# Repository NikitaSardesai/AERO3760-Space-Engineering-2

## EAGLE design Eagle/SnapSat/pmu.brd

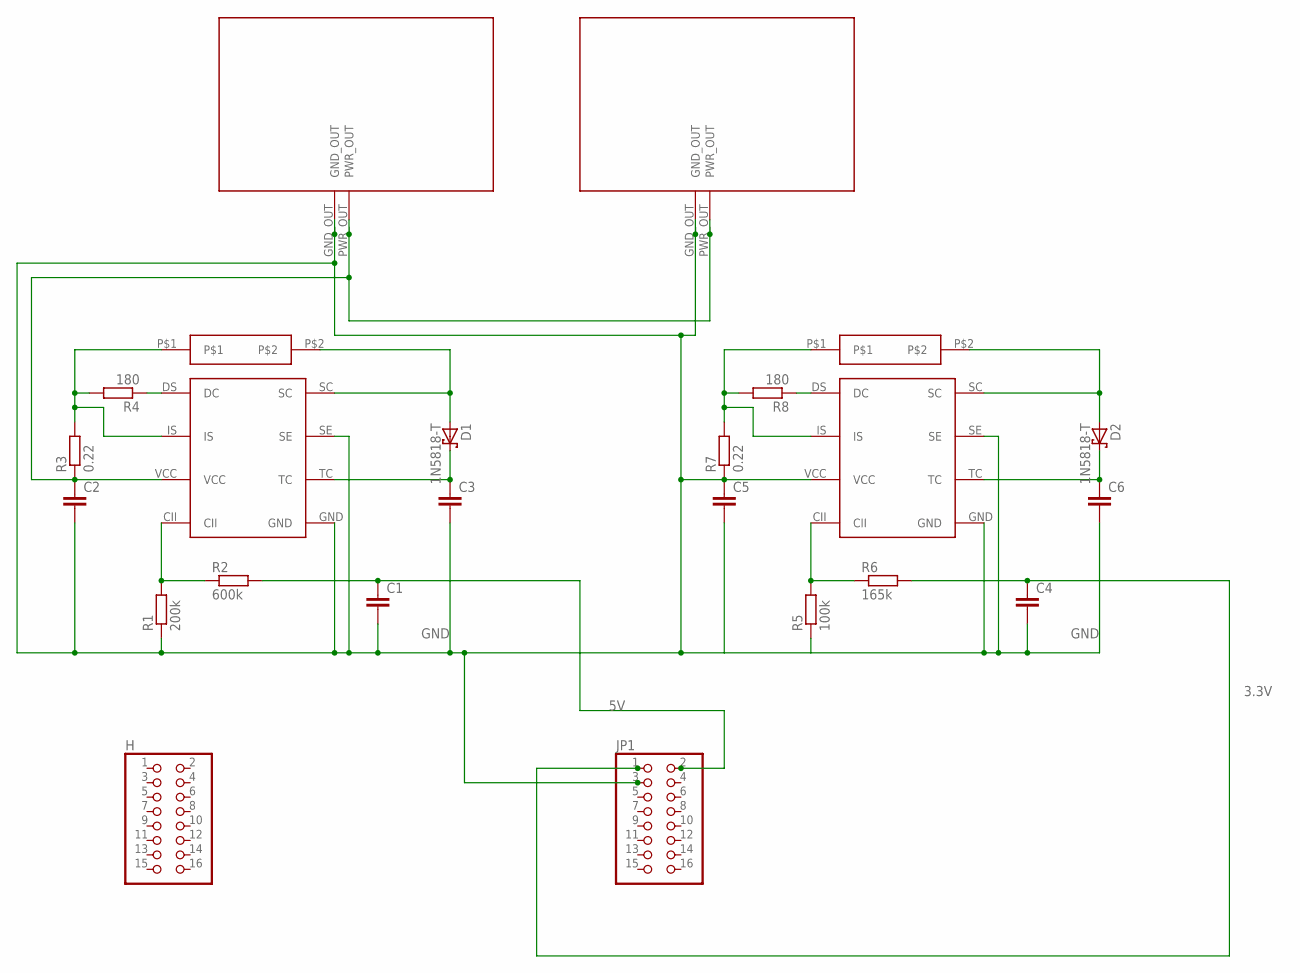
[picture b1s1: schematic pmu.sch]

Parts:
C1, C2, C3, C4, C5, C6: C2.5/6; C2.5-6
D1, D2: 1N5818-T; DO41-7.6
H: PINHD-2X8; 2X08
JP1: PINHD-2X8; 2X08
R1: 200k; 0207/12
R2: 600k; 0207/12
R3, R7: 0.22; 0207/12
R4, R8: 180; 0207/12
R5: 100k; 0207/12
R6: 165k; 0207/12
U$1, U$2: CHAR
U$3, U$5: TIBB
U$4, U$6: IND; 8RHT2

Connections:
3.3V: C4.1, JP1.1, R6.2
5V: C1.1, JP1.2, R2.2
GND: C1.2, C2.2, C3.2, C4.2, C5.1, C5.2, C6.2, JP1.3, R1.1, R5.1, R7.1, U$1.GND_OUT, U$2.GND_OUT, U$3.GND, U$3.SE, U$5.GND, U$5.SE, U$5.VCC
unnamed: D1.A, U$3.SC, U$4.P$2
unnamed: C2.1, R3.1, U$1.PWR_OUT, U$2.PWR_OUT, U$3.VCC
unnamed: R1.2, R2.1, U$3.CII
unnamed: R4.1, U$3.DS (DC)
unnamed: C3.1, D1.C, U$3.TC
unnamed: R5.2, R6.1, U$5.CII
unnamed: R3.2, R4.2, U$3.IS, U$4.P$1
unnamed: R7.2, R8.2, U$5.IS, U$6.P$1
unnamed: R8.1, U$5.DS (DC)
unnamed: D2.A, U$5.SC, U$6.P$2
unnamed: C6.1, D2.C, U$5.TC

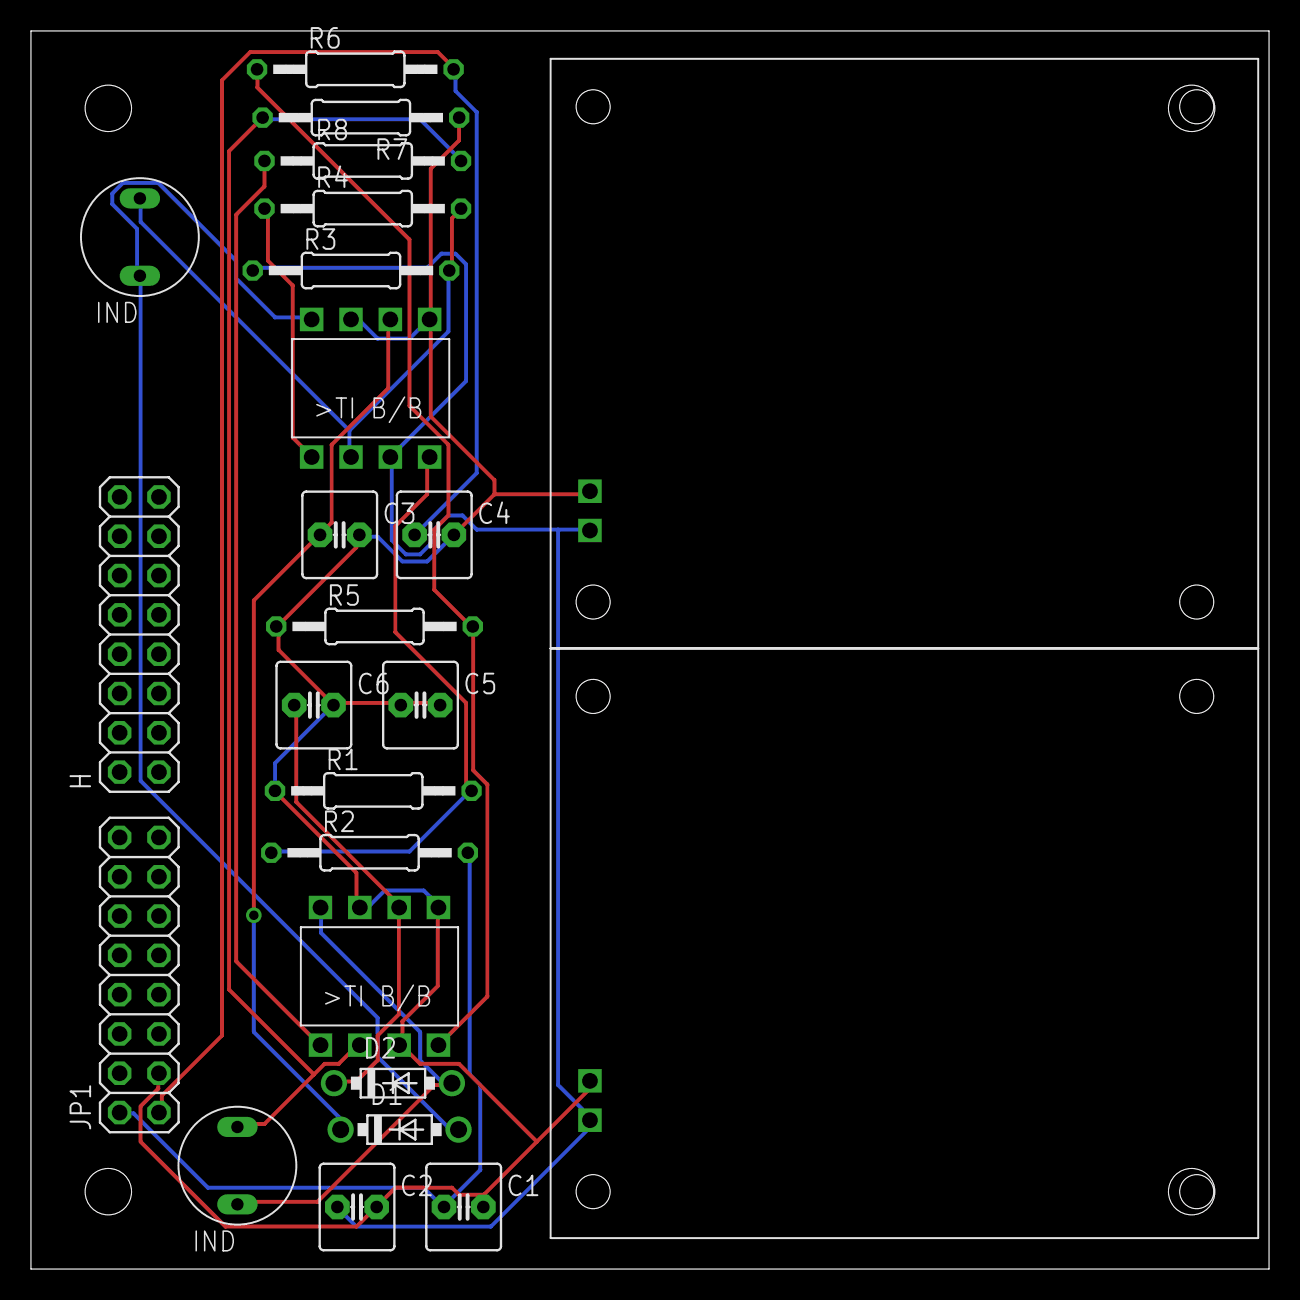
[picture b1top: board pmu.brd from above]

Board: 2 copper layers, 80.0 x 80.0 mm, 24 parts (0 on the bottom side), 14 nets.

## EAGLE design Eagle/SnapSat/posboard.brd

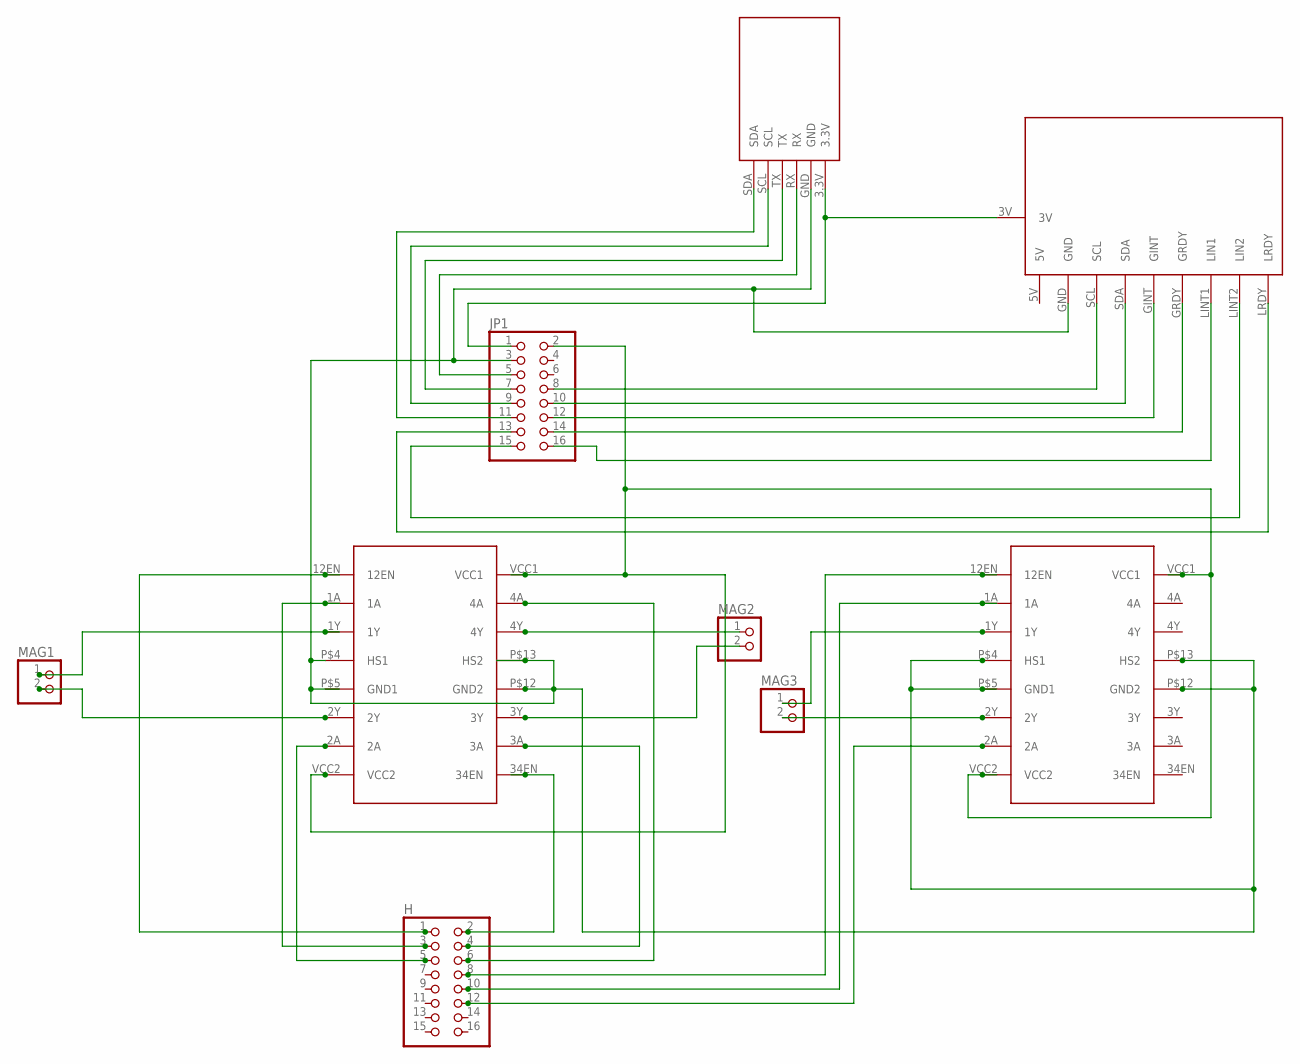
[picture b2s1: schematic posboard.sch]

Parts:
H: PINHD-2X8; 2X08
JP1: PINHD-2X8; 2X08
MAG1, MAG2, MAG3: PINHD-1X2; 1X02
U$1: GPS
U$2: IMU
U$3, U$4: HBRIDGE

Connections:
unnamed: JP1.1, U$1.3.3V, U$2.3V
unnamed: JP1.3, U$1.GND, U$2.GND, U$3.P$4 (HS1), U$3.P$12 (GND2), U$3.P$13 (HS2), U$4.P$4 (HS1), U$4.P$5 (GND1), U$4.P$12 (GND2), U$4.P$13 (HS2)
unnamed: JP1.5, U$1.RX
unnamed: JP1.7, U$1.TX
unnamed: JP1.9, U$1.SCL
unnamed: JP1.11, U$1.SDA
unnamed: H.1, U$3.12EN
unnamed: JP1.13, U$2.LRDY
unnamed: JP1.15, U$2.LINT2 (LIN2)
unnamed: JP1.16, U$2.LINT1 (LIN1)
unnamed: JP1.14, U$2.GRDY
unnamed: JP1.12, U$2.GINT
unnamed: JP1.10, U$2.SDA
unnamed: JP1.8, U$2.SCL
unnamed: H.3, U$3.1A
unnamed: JP1.2, U$3.VCC1, U$3.VCC2, U$4.VCC1, U$4.VCC2
unnamed: H.2, U$3.34EN
unnamed: H.4, U$3.3A
unnamed: H.5, U$3.2A
unnamed: H.8, U$4.12EN
unnamed: H.10, U$4.1A
unnamed: H.6, U$3.4A
unnamed: H.12, U$4.2A
unnamed: MAG1.1, U$3.1Y
unnamed: MAG1.2, U$3.2Y
unnamed: MAG2.1, U$3.4Y
unnamed: MAG2.2, U$3.3Y
unnamed: MAG3.1, U$4.1Y
unnamed: MAG3.2, U$4.2Y

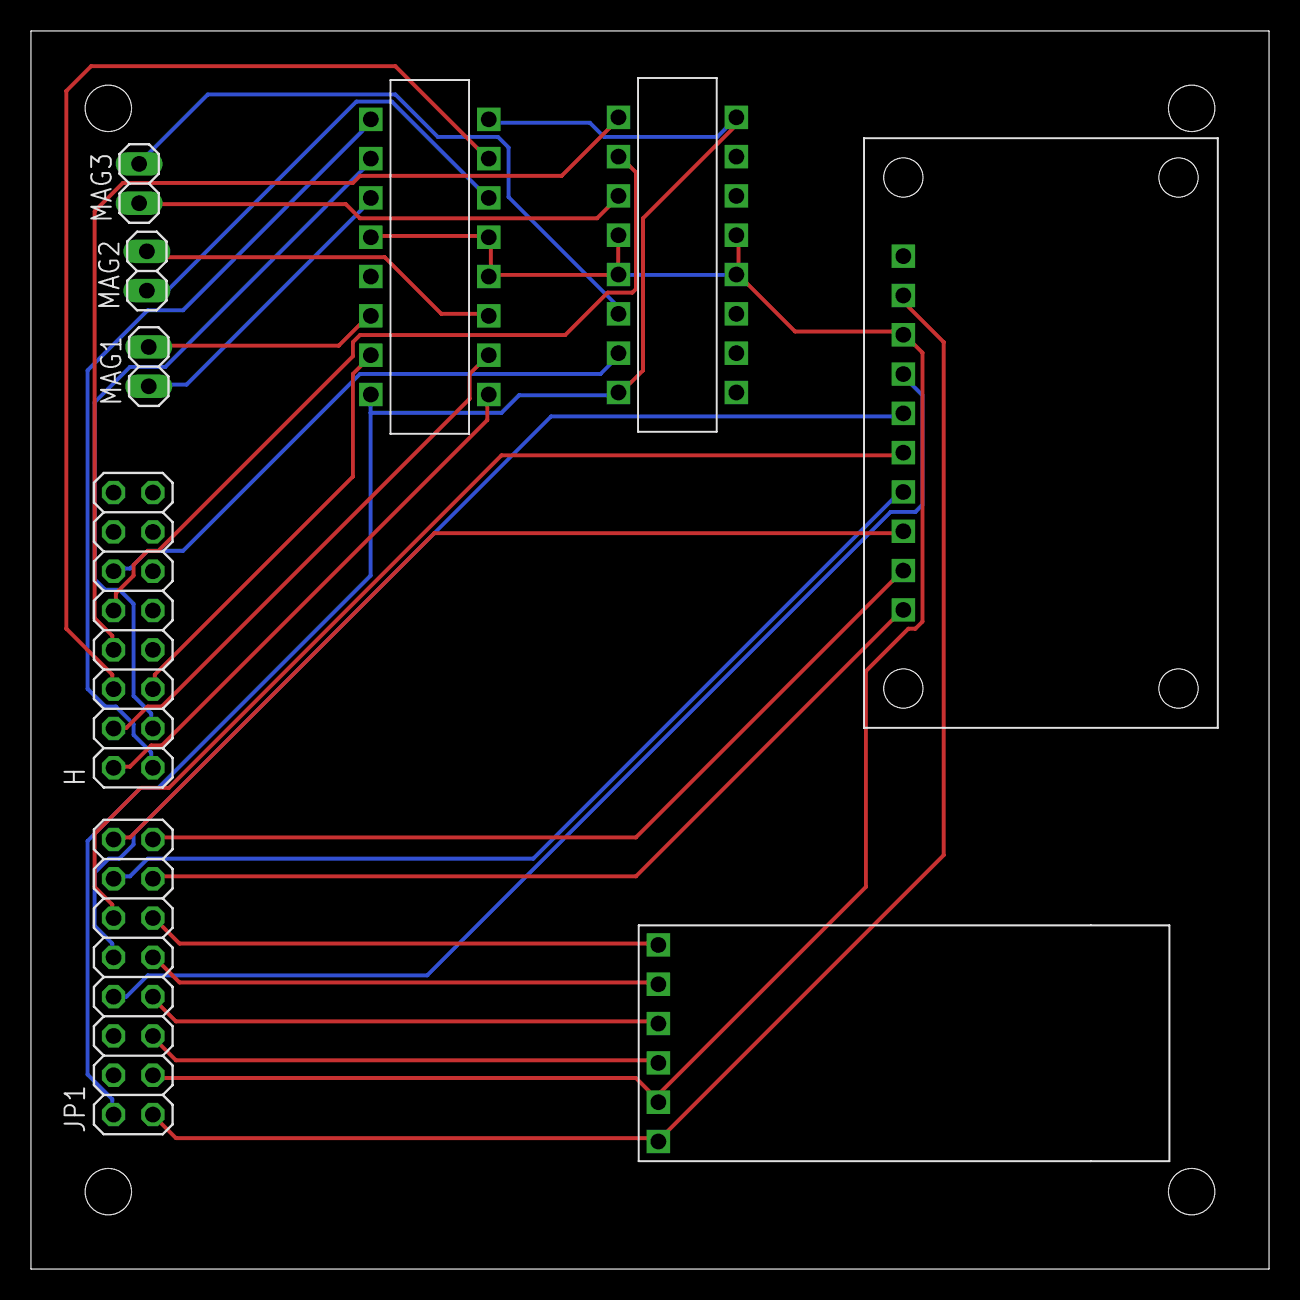
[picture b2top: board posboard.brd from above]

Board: 2 copper layers, 80.0 x 80.0 mm, 9 parts (0 on the bottom side), 29 nets.

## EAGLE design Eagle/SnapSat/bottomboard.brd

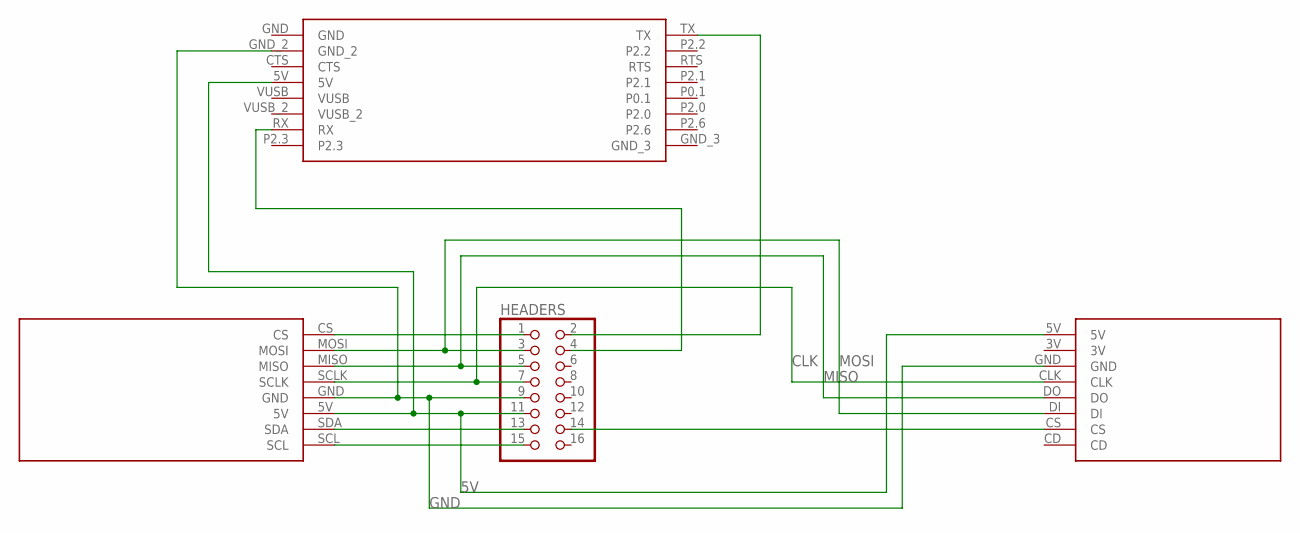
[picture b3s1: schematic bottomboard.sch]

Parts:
HEADERS: PINHD-2X8; 2X08
U$1: COMMS
U$2: SDCARD
U$3: ARDUCAM

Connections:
5V: HEADERS.11, U$1.5V, U$2.5V, U$3.5V
CLK: HEADERS.7, U$2.CLK, U$3.SCLK
GND: HEADERS.9, U$1.GND_2, U$2.GND, U$3.GND
MISO: HEADERS.5, U$2.DO, U$3.MISO
MOSI: HEADERS.3, U$2.DI, U$3.MOSI
unnamed: HEADERS.1, U$3.CS
unnamed: HEADERS.14, U$2.CS
unnamed: HEADERS.2, U$1.TX
unnamed: HEADERS.4, U$1.RX
unnamed: HEADERS.13, U$3.SDA
unnamed: HEADERS.15, U$3.SCL

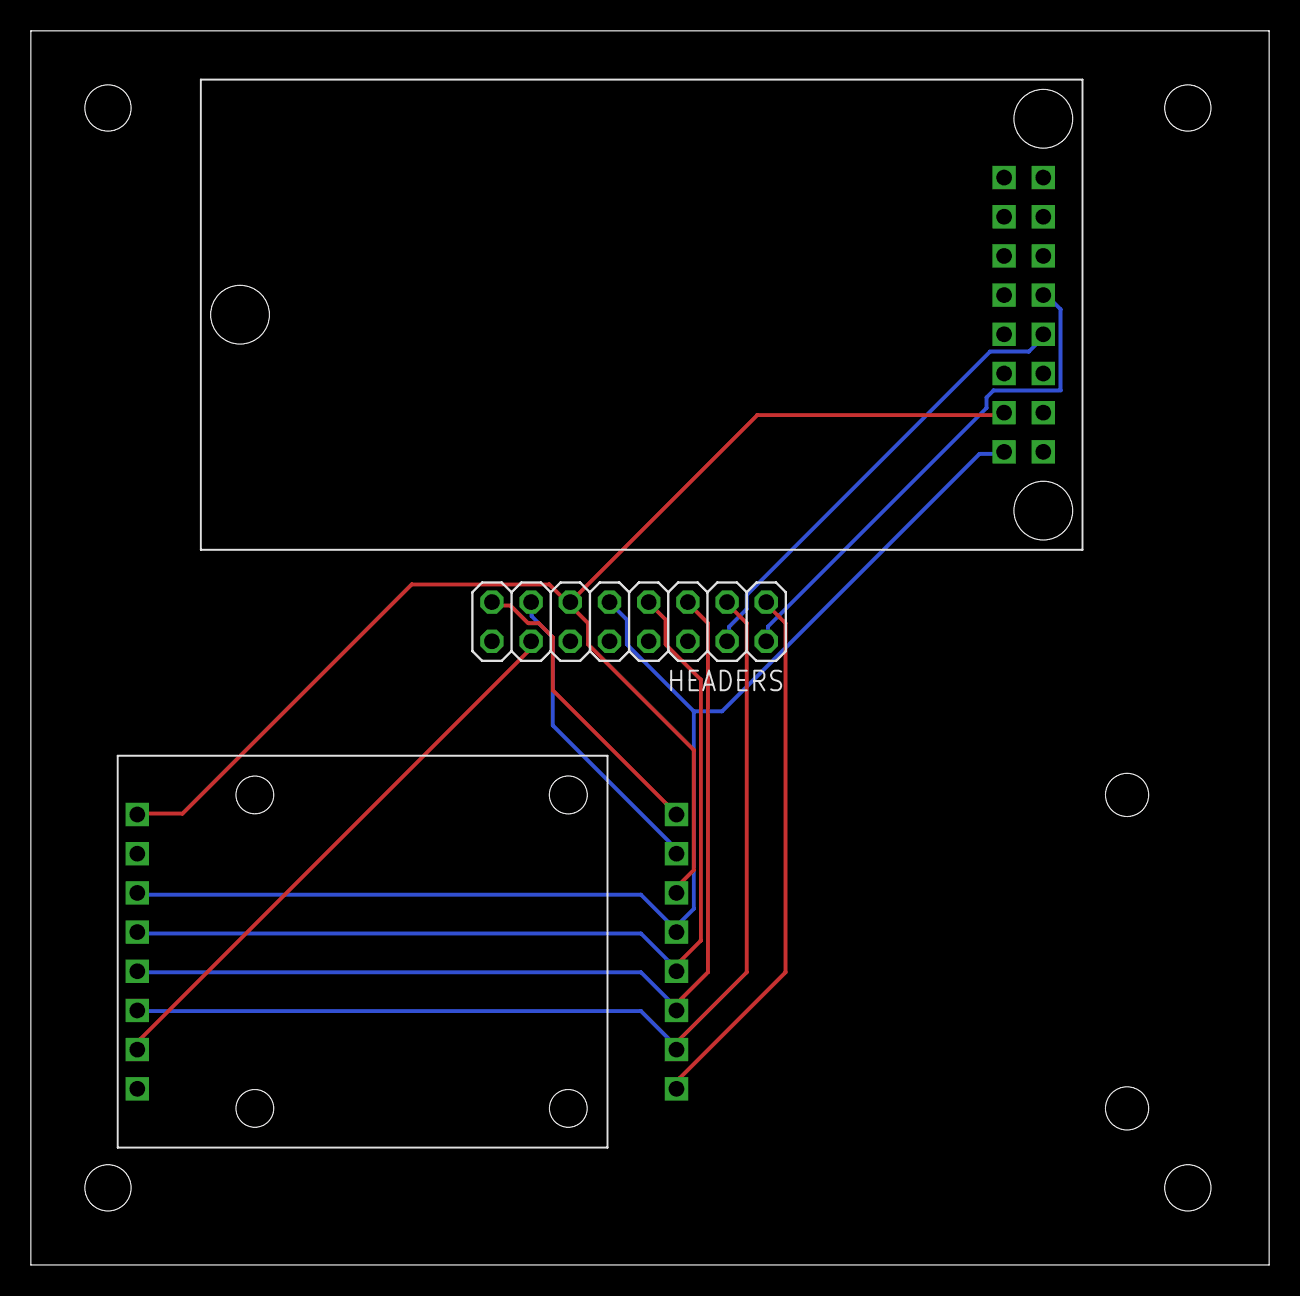
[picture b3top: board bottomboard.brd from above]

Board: 2 copper layers, 80.3 x 80.0 mm, 4 parts (1 on the bottom side), 11 nets.

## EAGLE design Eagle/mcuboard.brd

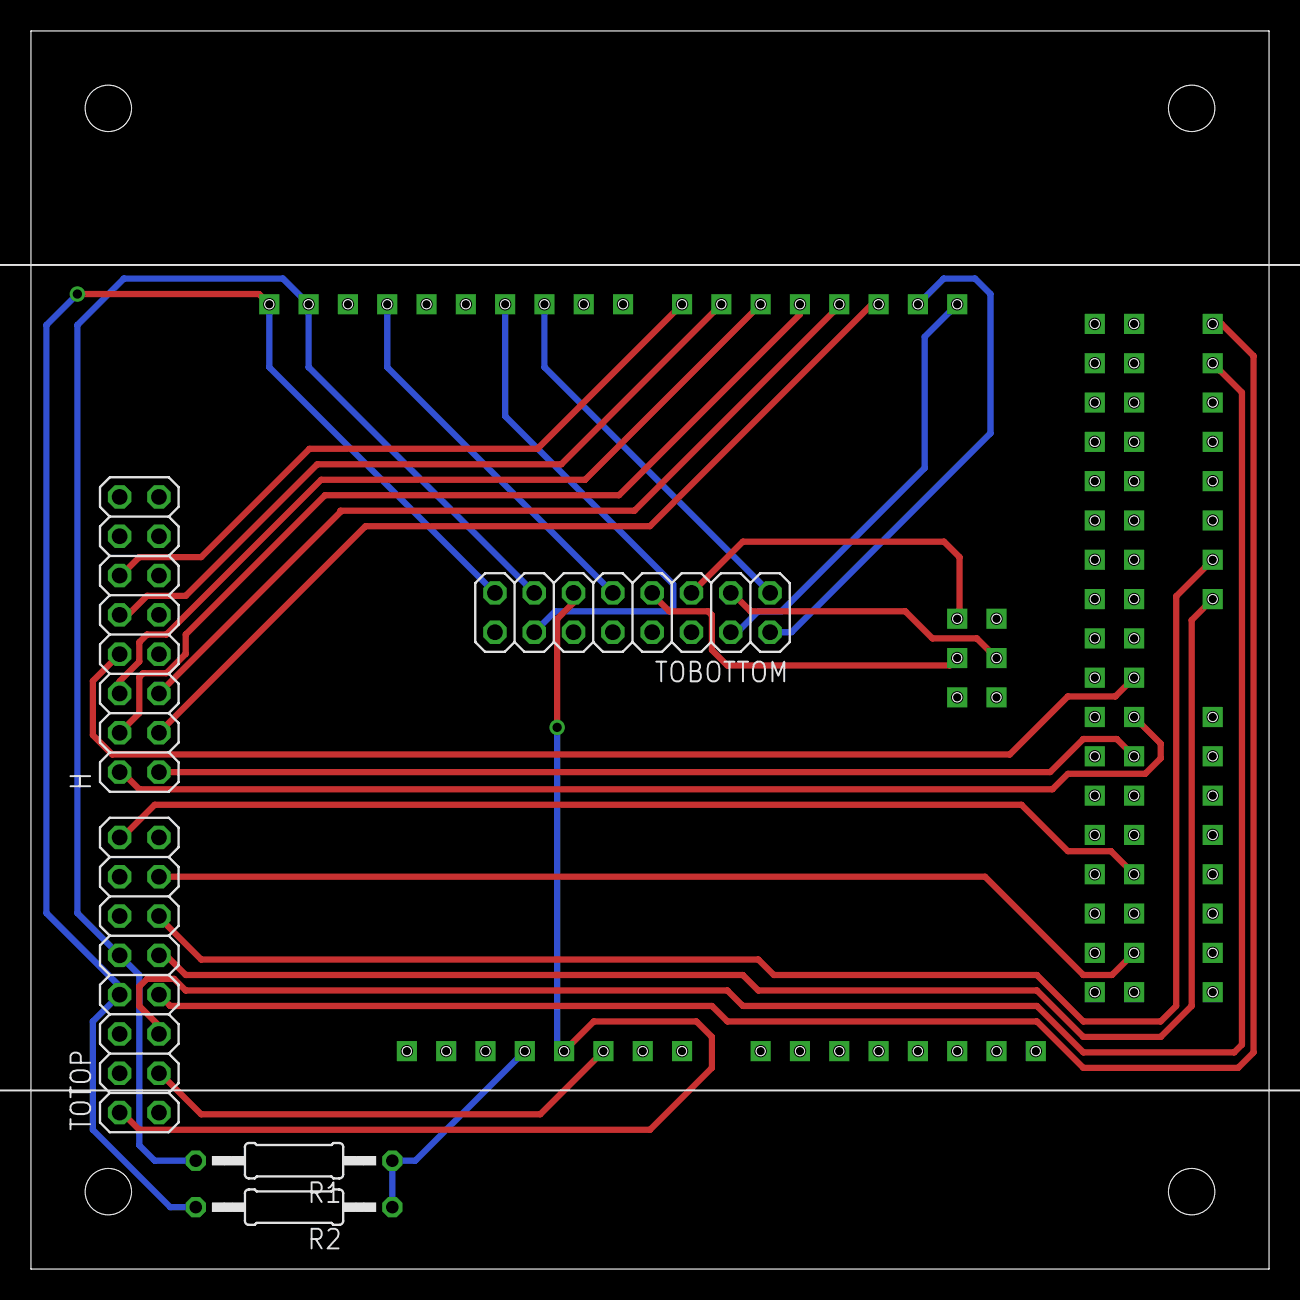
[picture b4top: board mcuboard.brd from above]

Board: 2 copper layers, 80.0 x 80.0 mm, 6 parts (0 on the bottom side), 28 nets.

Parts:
H: 2X08
R1, R2: 0207/12
TOBOTTOM: 2X08
TOTOP: 2X08
U$1: IDUINO1; IDUINO_PAC

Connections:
unnamed: TOBOTTOM.7, U$1.SPCK
unnamed: TOBOTTOM.3, U$1.MOSI
unnamed: TOBOTTOM.5, U$1.MISO
unnamed: TOBOTTOM.9, U$1.GND_H
unnamed: TOBOTTOM.11, TOTOP.2, U$1.5V
unnamed: R1.2, TOBOTTOM.13, TOTOP.10, U$1.SDA1
unnamed: R2.2, TOBOTTOM.15, TOTOP.8, U$1.SCL1
unnamed: TOBOTTOM.2, U$1.TX0
unnamed: TOTOP.3, U$1.GND_A1
unnamed: TOBOTTOM.4, U$1.RX0
unnamed: TOBOTTOM.14, U$1.11
unnamed: TOBOTTOM.1, U$1.10
unnamed: TOTOP.5, U$1.RX3
unnamed: TOTOP.7, U$1.TX3
unnamed: TOTOP.9, U$1.SCL
unnamed: TOTOP.11, U$1.SDA
unnamed: R1.1, R2.1, U$1.3.3V
unnamed: TOTOP.13, U$1.53
unnamed: TOTOP.16, U$1.49
unnamed: H.1, U$1.43
unnamed: H.8, U$1.39
unnamed: H.3, U$1.2
unnamed: H.5, U$1.3
unnamed: H.4, U$1.4
unnamed: H.2, U$1.41
unnamed: H.10, U$1.6
unnamed: H.12, U$1.7
unnamed: H.6, U$1.5

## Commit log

2015-08-10 :circus_tent: Added .gitattributes & .gitignore files
2015-08-10 Created Repository
    Added files and prelim formatting
2015-08-10 Final Template
    Put in Xiaoengs's template from Word - all that' left is to fill it
    in...
2015-08-10 Updated SpacecraftModesOfOperation
    Testing that this works without issues
2015-08-12 Minor formatting
2015-08-12 Merge remote-tracking branch 'origin/master'
    Conflicts:
    main.pdf
2015-08-12 Gantt Chart
    Added in an incomplete Gantt Chart - to complete (please ignore the mess
    that is the Project Plans file!)
2015-08-12 updated Modes of operation and added documents folder with CubeSat specs in it
2015-08-13 Gantt Update
2015-08-15 Updated Payload Design Overview
2015-08-17 An overview of the a cubeSat's communication system that I found online
2015-08-19 Component selection update
2015-08-20 Budgets upload
2015-08-20 Changes to ADCS masses
2015-08-20 Initial commit of Aluminium 6061 structure design
2015-08-20 budgets
    updated budgets, slight concern about power draw of camera - will ask
    D. Rye about it tomorrow
2015-08-21 Change to Power Requirements for Magnetorquers
2015-08-22 Payload design report updates (text)
2015-08-22 Quick Budgets Fix
2015-08-22 Pointing Budget
2015-08-22 Mass Balance Updates and Overview
2015-08-22 James' Section (Pointing Budget)
    appendix edited
    references updates
2015-08-22 Added in the Pointing Budget Section
2015-08-22 Just added a couple of things
2015-08-22 Edits and fixes. Updates overview section
2015-08-22 PRESENTATION
2015-08-22 Updated Table for Project Plans
2015-08-23 Updates to Mass budget
2015-08-23 pointing
2015-08-23 Mass Updates
2015-08-23 Updates
    updated mass budget and modes of operations
2015-08-23 Power
    finished Power Budget, finalized modes of operations
2015-08-23 budgets
    updated budgets
2015-08-23 minor changes
    budgets
2015-08-23 mass budget final update
2015-08-24 Final PDR and presentation updates
2015-08-24 Changed order of preso sections around a bit
2015-08-25 final presentation upload
2015-08-26 Folder reorganisation
2015-08-27 updated shopping list
2015-08-30 quick update
2015-08-30 Added Annex document
2015-08-31 Updated Annex
2015-09-06 annex
2015-09-07 final annex
2015-09-07 final final annexe
2015-09-12 CDR report beginning
    general outline for the CDR, starting to put all my thermal stuff in.
    Will also write a but about the payload.
    NoteL there are two other documents we also need to submit - will get
    started on these too
2015-09-13 Continuation of thermal section
    sundays updates.
    More to code once I've spoken to Xiaofeng regarding the orbit
    parameters.
2015-09-15 PCB layouts
    pcblayout
2015-09-19 Thermal Systems Report Update
2015-09-23 Moving along with the integration test plan
2015-09-23 Added the template of the code we will be using. It has some timer interrupts that all called utilising the library that is provided and an example hardware interrupt.
2015-09-24 Integration document update
    would be great if others worked on this.
2015-09-24 parsolid parts, might be able to open
2015-09-24 update on pcb
2015-10-05 updates and thermal
2015-10-11 Updates on thermal section
2015-10-12 eagle files
2015-10-12 eagle files 2
2015-10-12 library files
2015-10-15 Magnotorquers code
    This has the code for running the magnotorquer section. It takes the
    current location and desired location and outputs to the magnotorquers.
    We still need to write the comms code and mag code but imu is done
2015-10-15 edits to code
    updated code
2015-10-15 IMU data and libraries
    Added imu stuff to interruptcode
    Added libraries that you will need to install to run code
2015-10-18 card stuff
    card
2015-10-18 logging
    not interrupts, no timelog
2015-10-19 small updates
2015-10-19 fixed known pcb issues, small magnotorquer changes
2015-10-19 actual fixed pcbs
2015-10-19 extra breakouts
2015-10-21 got arducam writing to sd card
    ran out of program code on uno, further testing needs due
2015-10-25 Updates on the report
2015-10-28 thermal updates
2015-10-28 integration
    integrated to pcbs arducam to sd card
2015-10-28 small updates, will do more when thing is built
2015-10-29 PID Library and Integrated Code
2015-10-29 thermal
2015-10-29 Work on CDR_Tex
2015-10-29 Nothing
2015-10-29 fixes2
2015-10-29 EPS doneish
    need to add pictures, and check a few numbers
    referenced the datasheet, we lost marks for that last time
    needs proofreading
2015-10-29 thermal and system overview updates
2015-10-29 obc
    looking alright
2015-10-29 small changes, was trying to fix errors
2015-10-30 Link budgets added
2015-10-30 Communications system
2015-10-30 compilation updates: communications
2015-10-30 ANNEX UPDATE
2015-10-30 extended eps, added pictures
2015-10-30 more update
2015-10-30 change
2015-10-30 CDR update
2015-10-30 small eps edits, references and large obc addition
2015-11-04 presentation upload
2015-11-04 sd_cam_gps_imu should work just need to add comms
    + move in air thing
2015-11-04 comms merge
2015-11-04 CDR changes
2015-11-04 Updated comms, added delete functionality
2015-11-05 Working link
2015-11-06 added latest working code to repo
2015-11-06 made dummy code, untested, need libraries
2015-11-08 Added IMU libraries
2015-11-19 penny's changes
2015-11-23 IMU code
